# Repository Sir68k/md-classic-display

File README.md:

# md-classic-display

This project is a modern replacement for classic LCD displays in Sony MiniDisc portables. It uses an ATTiny1614 controller with a TPS61046 boost circuit for driving an SSD1306 OLED.

The protocol is documented here: https://github.com/MiniDisc-wiki/md-firmware/wiki/LCD-SPI-protocol-(NetMD-devices)

Confirmed to work with: MZ-N510, MZ-N520, MZ-N505. Should work on all Sony NetMD devices (non-himd), and most likely will work on older devices (the MZ-R700 uses the exact samedisplay protocol, I only haven't tested it).

## How to use

Connect the OLED board to the SPI lines on the MD display board. VCC on the display board isn't stable enough, you should connect to a stable voltage line on the MD controller board (such as VCC for the remote, VCO1 on the MZ-N510).

## What needs to be improved

- I haven't implemented custom glyph support yet, so my tetris / raycaster demos will not work with this display
- There can be minor lag between two display updates, which sometimes is visible when text is scrolling. Can be fixed by updating the display in a slightly smarter way.
- Themes would be cool

## Photos

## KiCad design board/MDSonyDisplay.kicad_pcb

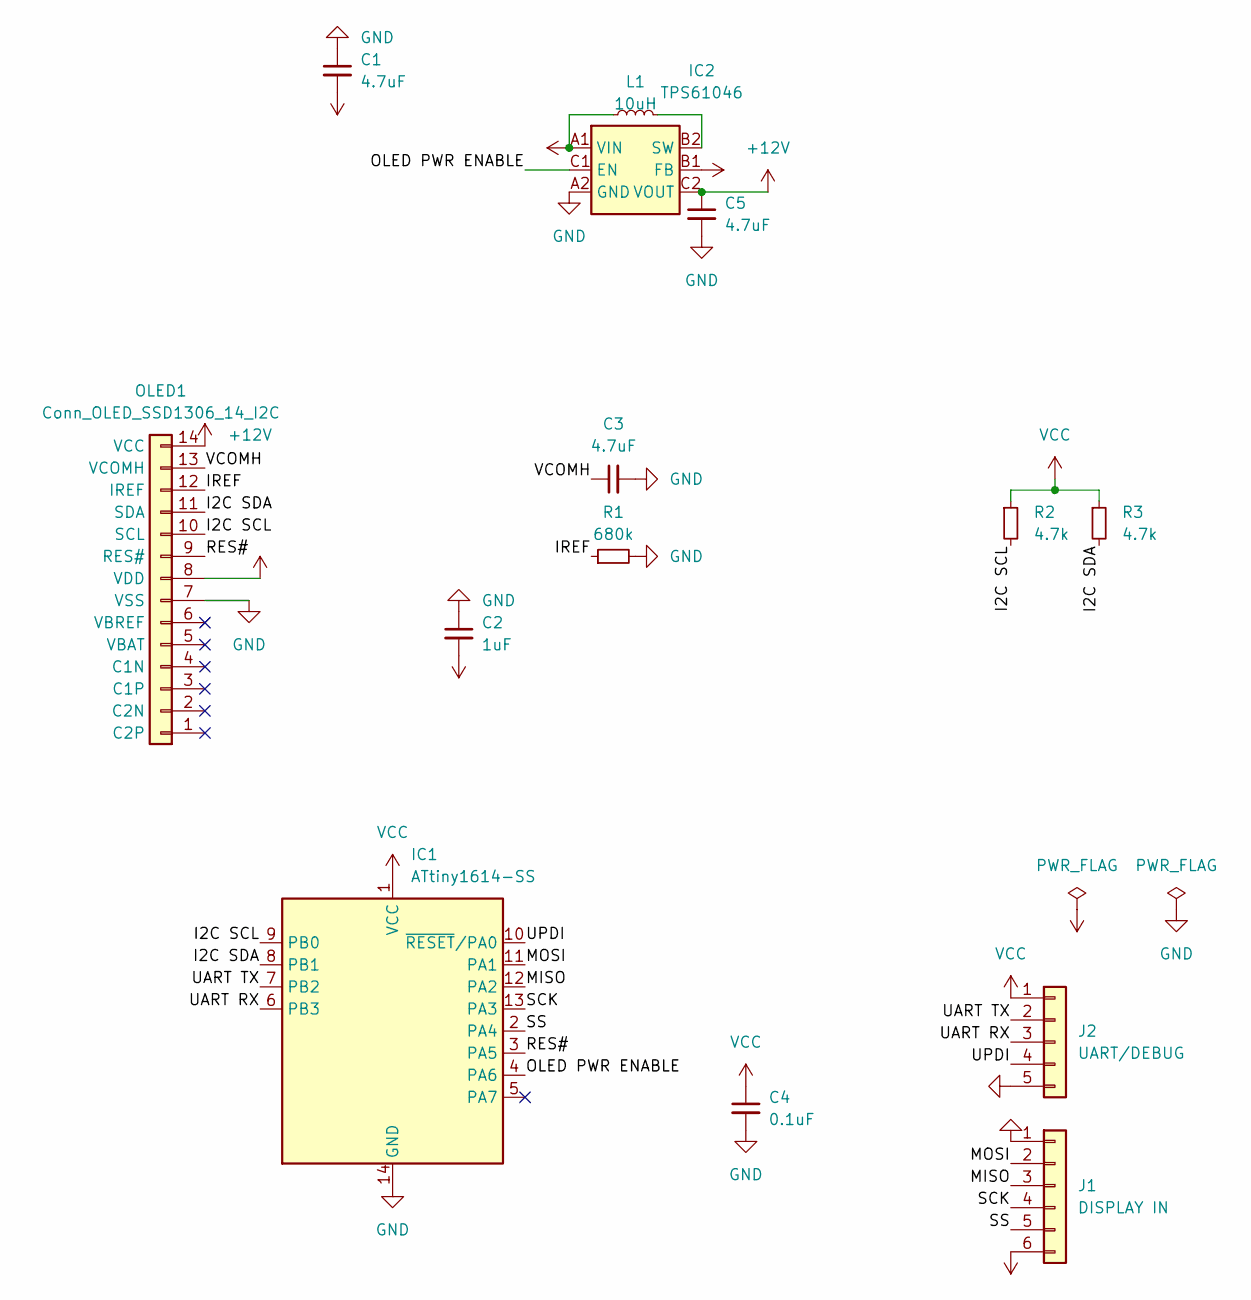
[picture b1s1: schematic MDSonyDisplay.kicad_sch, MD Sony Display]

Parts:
C1, C3, C5: 4.7uF; C_0603_1608Metric
C2: 1uF; C_0603_1608Metric
C4: 0.1uF; C_0402_1005Metric
IC1: ATtiny1614-SS; SOIC-14_3.9x8.7mm_P1.27mm
IC2: TPS61046; Texas_DSBGA-6_0.95x1.488mm_Layout2x3_P0.4mm
J1: DISPLAY IN; PinHeader_1x06_P1.00mm_Vertical
J2: UART/DEBUG; PinHeader_1x05_P1.00mm_Vertical
L1: 10uH; L_1008_2520Metric
OLED1: Conn_OLED_SSD1306_14_I2C; Connector_OLED_SSD1306_UT-0206-P02
R1: 680k; R_0603_1608Metric
R2, R3: 4.7k; R_0402_1005Metric

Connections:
+12V: C5.1, IC2.C2 (VOUT), OLED1.14 (VCC)
/I2C SCL: IC1.9 (PB0), OLED1.10 (SCL), R2.2
/I2C SDA: IC1.8 (PB1), OLED1.11 (SDA), R3.2
/IREF: OLED1.12 (IREF), R1.1
/MISO: IC1.12 (PA2), J1.3
/MOSI: IC1.11 (PA1), J1.2
/OLED PWR ENABLE: IC1.4 (PA6), IC2.C1 (EN)
/RES#: IC1.3 (PA5), OLED1.9 (RES#)
/SCK: IC1.13 (PA3), J1.4
/SS: IC1.2 (PA4), J1.5
/UART RX: IC1.6 (PB3), J2.3
/UART TX: IC1.7 (PB2), J2.2
/UPDI: IC1.10 (~RESET/PA0), J2.4
/VCOMH: C3.1, OLED1.13 (VCOMH)
GND: C1.1, C2.1, C3.2, C4.2, C5.2, IC1.14 (GND), IC2.A2 (GND), J1.1, J2.5, OLED1.7 (VSS), R1.2
unnamed: IC2.B2 (SW), L1.2
VCC: C1.2, C2.2, C4.1, IC1.1 (VCC), IC2.A1 (VIN), IC2.B1 (FB), J1.6, J2.1, L1.1, OLED1.8 (VDD), R2.1, R3.1

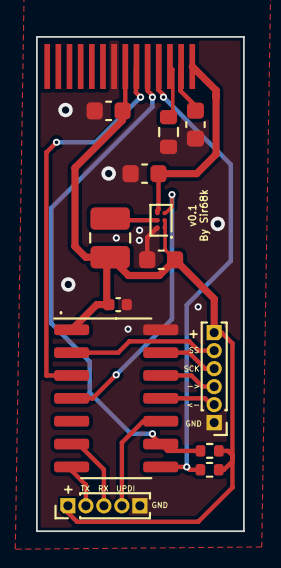
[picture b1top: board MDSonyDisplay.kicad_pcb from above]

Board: 2 copper layers, 11.5 x 27.5 mm, 14 parts (0 on the bottom side), 17 nets.

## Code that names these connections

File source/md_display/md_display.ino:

#include "oled.hpp"
#include "lcd_emu.h"
#include "icons.h"

#include <SPI.h>
#include <avr/io.h>
#include <avr/interrupt.h>

///////////
/// SPI ///
///////////

void SPI0_init(void);

/* SPI as Slave
 * Pin Assignment
 * 2. PA4 : SS
 * 11.PA1 : MOSI
 * 12.PA2 : MISO
 * 13.PA3 : SCK
 */
 
#define MOSI_bp 1
#define MOSI_bm (1 << MOSI_bp)
#define MISO_bp 2
#define MISO_bm (1 << MISO_bp)

#define SCK_bp 3
#define SCK_bm (1 << SCK_bp)
#define SS_bp 4
#define SS_bm (1 << SS_bp)


void SPI0_init(void) 
{
  PORTA.DIRSET = MISO_bm;

  SPI0.CTRLB = SPI_MODE3;
  SPI0.CTRLA = SPI_DORD_bm    /* LSB is transmitted first */
    | SPI_ENABLE_bm           /* Enable module */
    | (!SPI_MASTER_bm);       /* SPI module in Slave mode */
    SPI0.INTCTRL = SPI_IE_bm; /* SPI Interrupt enable */
}

ISR(SPI0_INT_vect)
{
  //uint8_t receiveData = SPI0.DATA;
  lcd_byte_in((uint8_t)SPI0.DATA);
  SPI0.DATA = 0;
  SPI0.INTFLAGS = SPI_IF_bm; /* Clear the Interrupt flag by writing 1 */
}

//////////
// OLED //
//////////

OLED<SSD1306_128x32> oled;

///////////
// SETUP //
///////////

void setup() {
  //Serial.begin(9600);

  SPI0_init();
  sei();

  pinMode(PIN_PA6, OUTPUT);
  digitalWrite(PIN_PA6, HIGH);


  pinMode(PIN_PA5, OUTPUT);
  digitalWrite(PIN_PA5, LOW);
  

  delay(100);
  digitalWrite(PIN_PA5, HIGH);
  
  oled.init();
  oled.flipV(1);
  oled.flipH(1);


  lcd_init();

  oled_intro();
  delay(250);
}

void oled_intro() {
  set_text_memory(0, 6, "Hello ");
  set_text_memory(6, 6, "World!");
  
  lcd_set_symbol(LCD_SYM_LP2, 1);
  lcd_set_symbol(LCD_SYM_MELODY, 1);
  lcd_set_symbol(LCD_SYM_REC, 1);
  lcd_set_symbol(LCD_SYM_SHUF, 1);
  lcd_set_symbol(LCD_SYM_SOUND1, 1);
  lcd_set_symbol(LCD_SYM_BOOKMARKED, 1);  

  lcd_set_symbol(LCD_SYM_BAT_BOX, 1);
  lcd_set_symbol(LCD_SYM_BAT_2, 1);
  
  lcd_set_symbol(LCD_SYM_DISC_1, 1);
  lcd_set_symbol(LCD_SYM_DISC_2, 1);
  lcd_set_symbol(LCD_SYM_DISC_3, 1);
  
  display_n510();
}

void loop() {
  display_n510();
}


void display_n510() {
  uint8_t  shift     = lcd_get_shift();

  oled.clear();
  oled.home();

  oled.setScale(1);

  ////////////////
  // AUDIO TYPE //
  ////////////////
    
  if (lcd_get_symbol(LCD_SYM_MONO))
    oled.drawString("MONO");
  else if (lcd_get_symbol(LCD_SYM_LP2))
    oled.drawString("LP2");
  else if (lcd_get_symbol(LCD_SYM_LP4))
    oled.drawString("LP4");
  else
    oled.drawString("SP");

  ////////////////////
  // SOUND SETTINGS //
  ////////////////////

  if (lcd_get_symbol(LCD_SYM_SOUND1))
    oled.drawString("/S1");
  else if (lcd_get_symbol(LCD_SYM_SOUND2))
    oled.drawString("/S2");

  ///////////////
  // PLAY MODE //
  ///////////////

  if (lcd_get_symbol(LCD_SYM_SHUF))
    oled.drawString("/SHUF");
  else if (lcd_get_symbol(LCD_SYM_REPEAT))
    oled.drawString("/REP");
  else if (lcd_get_symbol(LCD_SYM_SINGLE))
    oled.drawString("/1");

  ///////////
  // OTHER //
  ///////////

  if (lcd_get_symbol(LCD_SYM_SYNC))
    oled.drawString("/SYNC");

  if (lcd_get_symbol(LCD_SYM_BOOKMARKED))
    oled.drawString("/\xA3\xA4"); // bookmark char
  
  /////////
  // REC //
  /////////
  
  if (lcd_get_symbol(LCD_SYM_REC)) {
    oled.setCursorXY(128-14, 0);
    oled.drawString("\x98\x99"); // rec char
  }

  /////////////
  // BATTERY //
  /////////////



  if (lcd_get_symbol(LCD_SYM_BAT_BOX)) {
      uint8_t* battery_icon;

     if (lcd_get_symbol(LCD_SYM_BAT_4))
      battery_icon = icons_7x7[9];
     else if (lcd_get_symbol(LCD_SYM_BAT_3))
      battery_icon = icons_7x7[10];
     else if (lcd_get_symbol(LCD_SYM_BAT_2))
      battery_icon = icons_7x7[11];
     else if (lcd_get_symbol(LCD_SYM_BAT_1))
      battery_icon = icons_7x7[12];
     else
      battery_icon = icons_7x7[13];

     oled.drawIcon7(battery_icon, 118, 12);
  }


  //oled.drawIcon7(icons_7x7[4], 110, 11);

  /////////////////
  // DISC STATUS //
  /////////////////

  if (lcd_get_symbol(LCD_SYM_DISC_1))
    oled.fastLineV(127, 0, 9);

  if (lcd_get_symbol(LCD_SYM_DISC_2))
    oled.fastLineV(127, 11, 20);

  if (lcd_get_symbol(LCD_SYM_DISC_3))
    oled.fastLineV(127, 22, 31);

  ////////////////
  // LABEL MODE //
  ////////////////


  oled.setCursorXY(0, 10);
  
  if (lcd_get_symbol(LCD_SYM_MELODY))
    oled.drawString("\x94\x95"); // melody char
  if (lcd_get_symbol(LCD_SYM_FOLDER))
    oled.drawString("\x92\x93"); // folder char
  
  /////////////////////
  // NUMBER SEGMENTS //
  /////////////////////
  
  draw7segment(92+ 0, 25, 0x7f);//lcd_get_7segment(1));
  draw7segment(92+ 6, 25, 0x7f);//lcd_get_7segment(2));
  draw7segment(92+12, 25, 0x7f);//lcd_get_7segment(3));

  if (lcd_get_symbol(LCD_SYM_SEG_COL)) {
    oled.setCursorXY(92+17, 25);
    oled.drawString(":");
  }

  draw7segment(92+22, 25, 0x7f);//lcd_get_7segment(4));
  draw7segment(92+28, 25, 0x7f);//lcd_get_7segment(5));
  
  ///////////////
  // TEXT DATA //
  ///////////////

  
  oled.setScale(2);
  oled.setCursorXY(0, 18);
  
  uint8_t* txt = lcd_get_text_data(0);
  for (int i=0; i<7; i++) {
    oled.drawChar(txt[i]);  
  }


  /*
  for (int r=0; r<3; r++) { 
    oled.setCursorXY(0, 9 + r*8);
    uint8_t* txt = lcd_get_text_data(r);
    
    for (int i=0; i<10; i++) {
      oled.drawChar(txt[i]);  
    }
  }*/
  
  oled.update();
  delay(10);
}

void draw7segment(uint8_t x, uint8_t y, uint8_t v) {

  // top segment
  if (v & 0b0000001){
    oled.dot(x+1, y, 1);  
    oled.dot(x+2, y, 1); 
    oled.dot(x+3, y, 1); 
  }

  // middle
  if (v & 0b0001000){
    oled.dot(x+1, y+3, 1);  
    oled.dot(x+2, y+3, 1); 
    oled.dot(x+3, y+3, 1); 
  }

  // bottom
  if (v & 0b1000000){
    oled.dot(x+1, y+6, 1);  
    oled.dot(x+2, y+6, 1); 
    oled.dot(x+3, y+6, 1); 
  }

  // top right
  if (v & 0b0000010){
    oled.dot(x+4, y+1, 1);  
    oled.dot(x+4, y+2, 1); 
  }

  // top left
  if (v & 0b0000100){
    oled.dot(x, y+1, 1);  
    oled.dot(x, y+2, 1); 
  }

  // bottom right
  if (v & 0b0010000){
    oled.dot(x+4, y+4, 1);  
    oled.dot(x+4, y+5, 1); 
  }

  // bottom left
  if (v & 0b0100000){
    oled.dot(x, y+4, 1);  
    oled.dot(x, y+5, 1); 
  }
}

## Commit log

2023-05-27 add all files
